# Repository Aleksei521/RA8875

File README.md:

# RA8875
 Board and font convertor for chip RA8875
 https://habr.com/ru/post/551820/#habracut

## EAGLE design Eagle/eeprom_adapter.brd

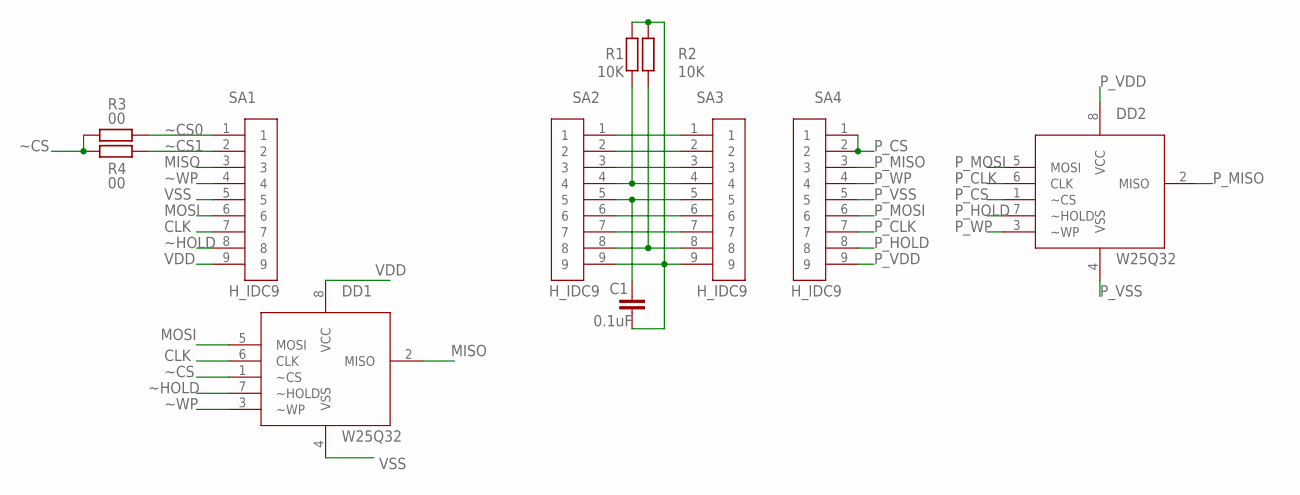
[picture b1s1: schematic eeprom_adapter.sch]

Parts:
C1: 0.1uF; C0603
DD1: W25Q32; SOIC-208
DD2: W25Q32; H_DIL08
R1, R2: 10K; R0603
R3, R4: 00; R0603
SA1, SA2, SA3, SA4: H_IDC9; H_IDC8X1_27

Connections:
CLK: DD1.6 (CLK), SA1.7
MISO: DD1.2 (MISO), SA1.3
MOSI: DD1.5 (MOSI), SA1.6
unnamed: SA2.1, SA3.1
unnamed: SA2.2, SA3.2
unnamed: SA2.3, SA3.3
unnamed: R1.1, SA2.4, SA3.4
unnamed: C1.1, SA2.5, SA3.5
unnamed: SA2.6, SA3.6
unnamed: SA2.7, SA3.7
unnamed: R2.1, SA2.8, SA3.8
unnamed: C1.2, R1.2, R2.2, SA2.9, SA3.9
P_CLK: DD2.6 (CLK), SA4.7
P_CS: DD2.1 (~CS), SA4.1, SA4.2
P_HOLD: DD2.7 (~HOLD), SA4.8
P_MISO: DD2.2 (MISO), SA4.3
P_MOSI: DD2.5 (MOSI), SA4.6
P_VDD: DD2.8 (VCC), SA4.9
P_VSS: DD2.4 (VSS), SA4.5
P_WP: DD2.3 (~WP), SA4.4
VDD: DD1.8 (VCC), SA1.9
VSS: DD1.4 (VSS), SA1.5
~CS: DD1.1 (~CS), R3.2, R4.2
~CS0: R3.1, SA1.1
~CS1: R4.1, SA1.2
~HOLD: DD1.7 (~HOLD), SA1.8
~WP: DD1.3 (~WP), SA1.4

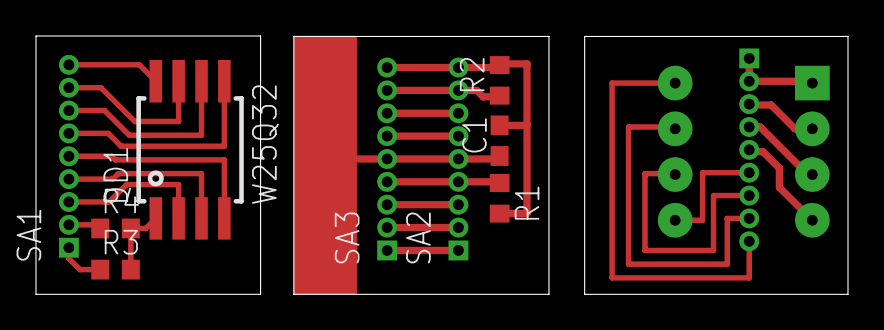
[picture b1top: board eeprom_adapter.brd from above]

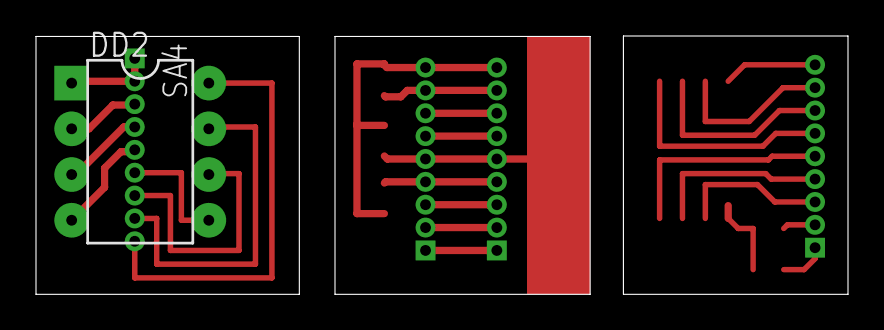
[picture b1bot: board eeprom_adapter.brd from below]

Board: 2 copper layers, 45.1 x 14.4 mm, 11 parts (2 on the bottom side), 27 nets.

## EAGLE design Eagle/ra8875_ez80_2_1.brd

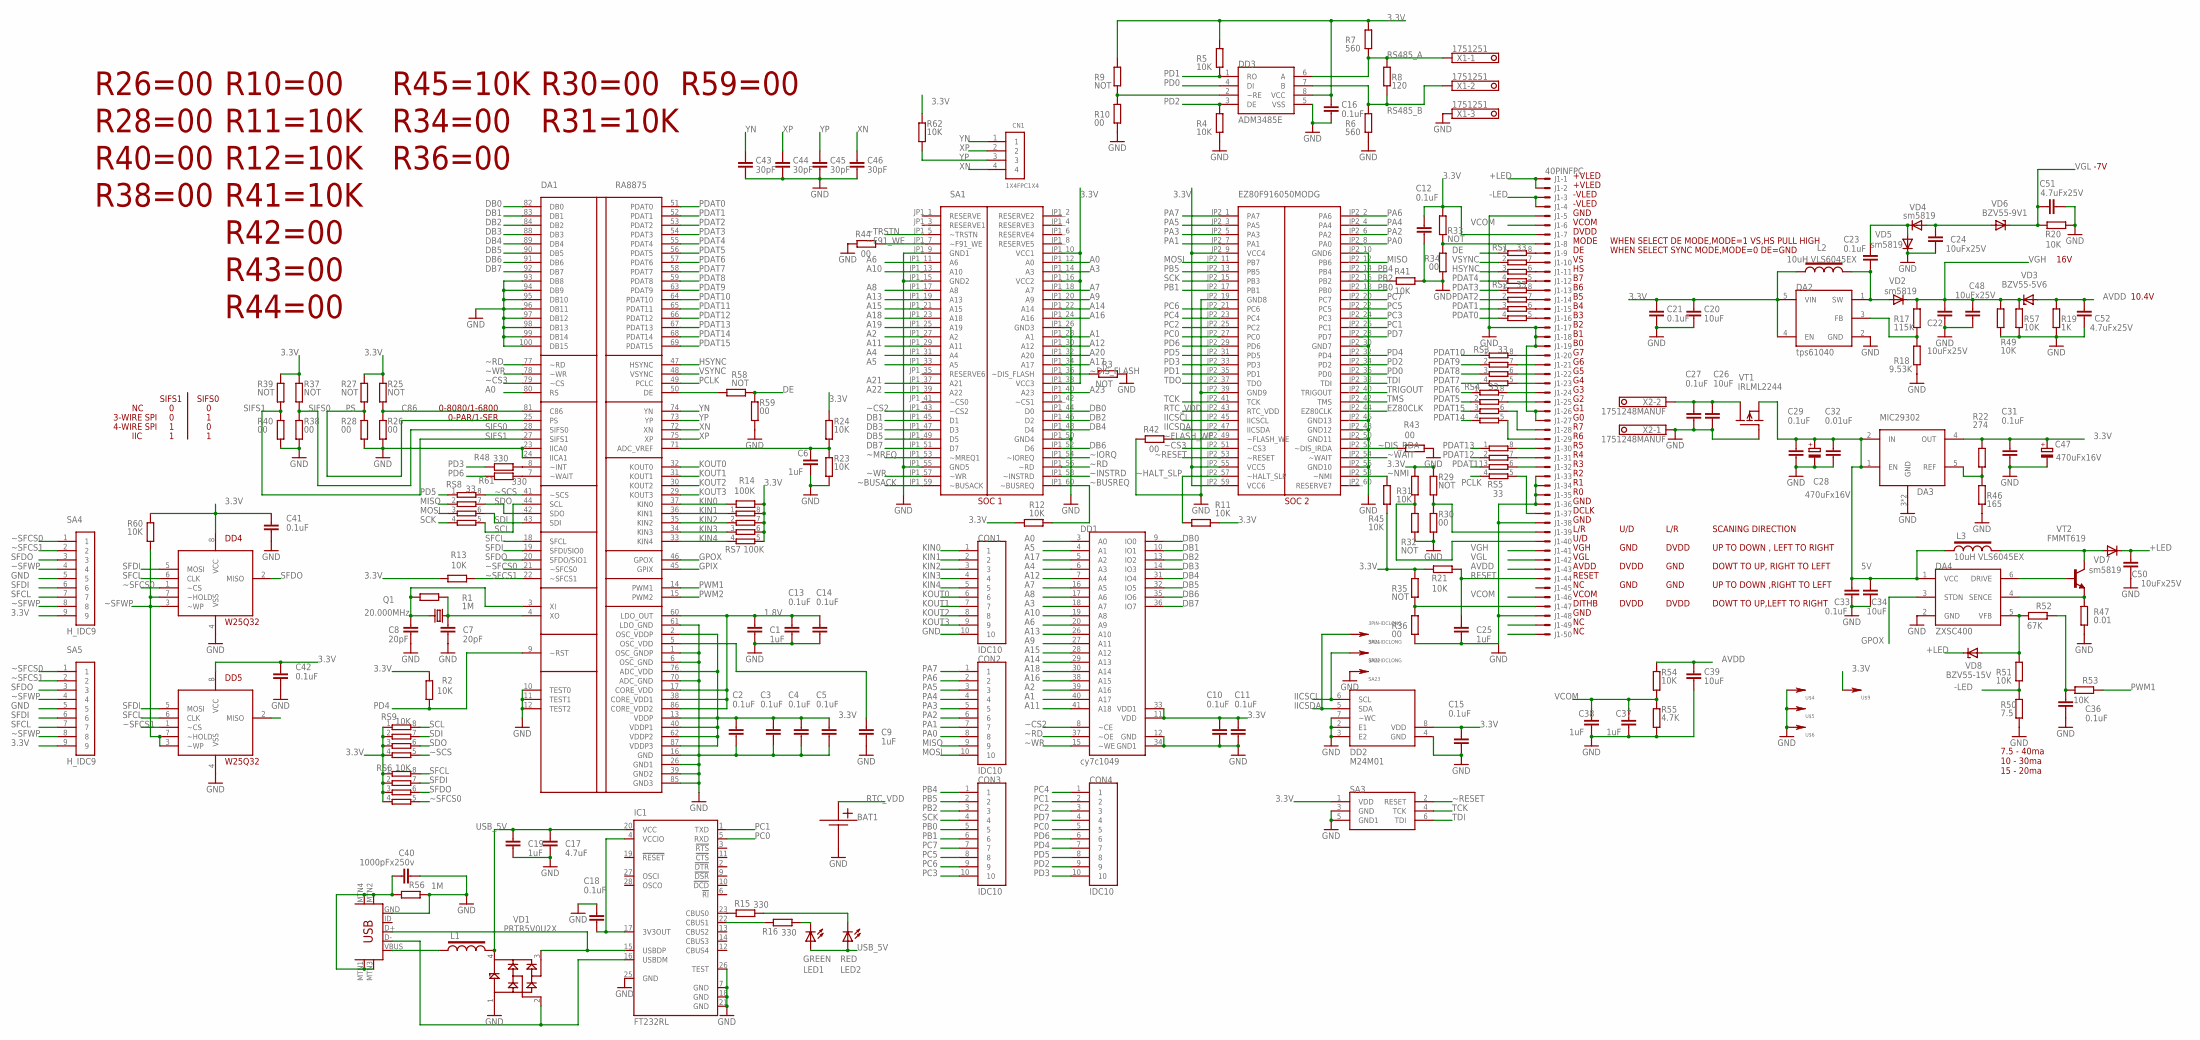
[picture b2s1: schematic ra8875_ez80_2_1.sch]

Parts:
BAT1: EECF5R5U155
C1, C6, C9, C19, C25, C37, C38: 1uF; C0603
C2, C3, C4, C5, C10, C11, C12, C13, C14, C15, C16, C18, C41, C42: 0.1uF; C0603
C7, C8: 20pF; C0805
C17: 4.7uF; C0805
C20, C26, C34, C39: 10uF; C1206
C21, C27, C29, C31, C33, C36: 0.1uF; C0805
C22, C24, C48, C50: 10uFx25V; C1206
C23: 0.1uF; C1206
C28, C47: 470uFx16V; SMC_D
C32: 0.01uF; C0805
C40: 1000pFx250v; C1812
C43, C44, C45, C46: 30pF; C0603
C51, C52: 4.7uFx25V; C1206
CN1: 1X4FPC1X4; FPC_1MM-4
CON1, CON2, CON3, CON4: IDC10
DA1: RA8875; LQFP100
DA2: tps61040; SOT23-5L
DA3: MIC29302; TO263-5
DA4: ZXSC400; SOT23-6L
DD1: cy7c1049; TSOP_Z44_II
DD2: M24M01; SOIC8
DD3: ADM3485E; SO8
DD4, DD5: W25Q32; SOIC-208
IC1: FT232RL; SSOP28
J1: 40PINFPC; 4-1734839-0
L1: USB_INDUCTOR; R0805
L2, L3: 10uH VLS6045EX; VLS6045
LED1: GREEN; CHIPLED_1206
LED2: RED; CHIPLED_1206
Q1: 20.000MHz; HC49U70
R1: 1M; R0603
R2, R4, R5, R11, R12, R13, R21, R23, R24, R31, R41, R45, R51, R53, R54, R60, R62: 10K; R0603
R3, R9, R25, R27, R29, R32, R33, R35, R37, R39, R58: NOT; R0603
R6, R7: 560; R0603
R8: 120; R0603
R10, R26, R28, R30, R34, R36, R38, R40, R42, R43, R44, R59: 00; R0603
R14: 100K; R0603
R15, R16, R48, R61: 330; R0603
R17: 115K; R0805
R18: 9.53K; R0805
R19: 1K; R0805
R20: 10K; R0805
R22: 274; R0805
R46: 165; R0805
R47: 0.01; R2512
R49, R57: 10K; R1206
R50: 7.5; R0805
R52: 67K; R0603
R55: 4.7K; R0603
R56: 1M; R1206
RS1, RS2, RS3, RS4, RS5, RS8: 33; CAY16-4
RS6, RS9: 10K; CAY16-4
RS7: 100K; CAY16-4
SA1: EZ80F916050MODG
SA2: 3PIN-IDCLONG; 3PIN-254
SA3: ZPAKII
SA4, SA5: H_IDC9; H_IDC8X1_27
U$3: USB-MINIB-5PIN; USB-MINIB
U$4, U$5, U$6, U$9: 1-PIN2_54; 1_PIN_2_54
VD1: PRTR5V0U2X; SOT143B
VD2, VD4, VD5, VD7: sm5819; MELF-MLL41
VD3: BZV55-5V6; STABILITRON
VD6: BZV55-9V1; STABILITRON
VD8: BZV55-15V; STABILITRON
VT1: IRLML2244; SOT23
VT2: FMMT619; SOT23-BEC
X1: 1751251
X2: 1751248MANUF; 1751248

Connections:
1.8V: C1.1, C13.1, C14.1, DA1.17 (CORE_VDD), DA1.38 (CORE_VDD1), DA1.60 (LDO_OUT), DA1.86 (CORE_VDD2)
3.3V: C2.1, C3.1, C4.1, C5.1, C10.1, C11.1, C12.1, C15.1, C16.1, C20.1, C21.1, C31.1, C41.1, C42.1, C47.+, DA1.2 (OSC_VDDP), DA1.13 (VDDP), DA1.40 (VDDP1), DA1.62 (VDDP2), DA1.76 (ADC_VDD), DA1.87 (VDDP3), DA2.4 (EN), DA2.5 (VIN), DA3.4 (OUT), DD1.11 (VDD), DD1.33 (VDD1), DD2.8 (VDD), DD3.8 (VCC), DD4.8 (VCC), DD5.8 (VCC), J1.7 (MS), L2.P$1 (L1), R2.2, R5.1, R7.1, R9.1, R11.1, R12.2, R13.1, R14.2, R21.1, R22.1, R24.1, R25.1, R27.1, R29.1, R31.1, R33.1, R35.1, R37.1, R39.1, R45.2, R60.1, R62.1, RS6.1, RS6.2, RS6.3, RS6.4, RS7.5, RS7.6, RS7.7, RS7.8, RS9.1, RS9.2, RS9.3, RS9.4, SA1.JP1_10 (VCC1), SA1.JP1_16 (VCC2), SA1.JP1_38 (VCC3), SA1.JP2_9 (VCC4), SA1.JP2_55 (VCC5), SA1.JP2_59 (VCC6), SA3.1 (VDD), SA4.9, SA5.9, U$9.P$1
5V: C28.+, C29.1, C32.1, C33.1, C34.1, DA3.1 (EN), DA3.2 (IN), DA4.1 (VCC), L3.P$1 (L1), VT1.2 (S)
+LED: C50.1, J1.1 (MSV), J1.2 (MS), VD7.C, VD8.C
-LED: J1.3 (MS), J1.4 (MS), R50.1, R51.2
A0: DA1.80 (RS), DD1.3 (A0), SA1.JP1_12 (A0)
A1: DD1.40 (A17), SA1.JP1_28 (A1)
A2: DD1.39 (A16), SA1.JP1_27 (A2)
A3: DD1.18 (A7), SA1.JP1_14 (A3)
A4: DD1.6 (A3), SA1.JP1_31 (A4)
A5: DD1.4 (A1), SA1.JP1_33 (A5)
A6: DD1.20 (A9), SA1.JP1_11 (A6)
A7: DD1.16 (A5), SA1.JP1_18 (A7)
A8: DD1.17 (A6), SA1.JP1_17 (A8)
A9: DD1.27 (A11), SA1.JP1_20 (A9)
A10: DD1.19 (A8), SA1.JP1_13 (A10)
A11: DD1.41 (A18), SA1.JP1_29 (A11)
A12: DD1.7 (A4), SA1.JP1_30 (A12)
A13: DD1.26 (A10), SA1.JP1_19 (A13)
A14: DD1.29 (A13), SA1.JP1_22 (A14)
A15: DD1.28 (A12), SA1.JP1_21 (A15)
A16: DD1.38 (A15), SA1.JP1_24 (A16)
A17: DD1.5 (A2), SA1.JP1_34 (A17)
A18: DD1.30 (A14), SA1.JP1_23 (A18)
A19: SA1.JP1_25 (A19)
A20: SA1.JP1_32 (A20)
A21: SA1.JP1_37 (A21)
A22: SA1.JP1_39 (A22)
A23: SA1.JP1_40 (A23)
ADC_VREF: C6.1, DA1.71 (ADC_VREF), R23.1, R24.2
AVDD: C39.1, C52.1, J1.43 (MS), R19.1, R54.1, VD3.A
C86: DA1.81 (C86), R25.2, R26.1
DB0: DA1.82 (DB0), DD1.9 (IO0), SA1.JP1_44 (D0)
DB1: DA1.83 (DB1), DD1.10 (IO1), SA1.JP1_45 (D1)
DB2: DA1.84 (DB2), DD1.13 (IO2), SA1.JP1_46 (D2)
DB3: DA1.88 (DB3), DD1.14 (IO3), SA1.JP1_47 (D3)
DB4: DA1.89 (DB4), DD1.31 (IO4), SA1.JP1_48 (D4)
DB5: DA1.90 (DB5), DD1.32 (IO5), SA1.JP1_49 (D5)
DB6: DA1.91 (DB6), DD1.35 (IO6), SA1.JP1_52 (D6)
DB7: DA1.92 (DB7), DD1.36 (IO7), SA1.JP1_51 (D7)
DE: R58.1, R59.1, RS1.1
EZ80CLK: SA1.JP2_44 (EZ80CLK)
GND: BAT1.- (MINUS), C1.2, C2.2, C3.2, C4.2, C5.2, C6.2, C7.2, C8.2, C9.2, C10.2, C11.2, C12.2, C13.2, C14.2, C15.2, C16.2, C17.2, C18.1, C19.2, C20.2, C21.2, C22.2, C24.2, C25.2, C26.2, C27.2, C28.-, C29.2, C31.2, C32.2, C33.2, C34.2, C36.2, C37.2, C38.2, C39.2, C40.2, C41.2, C42.2, C43.2, C44.2, C45.2, C46.2, C47.-, C48.2, C50.2, C51.2, C52.2, CON1.10, DA1.1 (OSC_GNDP), DA1.6 (OSC_GND), DA1.10 (TEST0), DA1.11 (TEST1), DA1.12 (TEST2), DA1.16 (GND), DA1.23 (IICA0), DA1.24 (IICA1), DA1.26 (GND1), DA1.39 (GND2), DA1.61 (LDO_GND), DA1.70 (ADC_GND), DA1.85 (GND3), DA1.93 (DB8), DA1.94 (DB9), DA1.95 (DB10), DA1.96 (DB11), DA1.97 (DB12), DA1.98 (DB13), DA1.99 (DB14), DA1.100 (DB15), DA2.2 (GND), DA3.3 (GND), DA3.6 (GND), DA4.2 (GND), DD1.12 (GND), DD1.34 (GND1), DD2.2 (E1), DD2.3 (E2), DD2.4 (GND), DD2.7 (~WC), DD3.5 (VSS), DD4.4 (VSS), DD5.4 (VSS), IC1.7 (GND), IC1.18 (GND), IC1.21 (GND), IC1.25 (GND), IC1.26 (TEST), J1.5 (MS), J1.17 (MS), J1.18 (MS), J1.19 (MS), J1.26 (MS), J1.27 (MS), J1.33 (MS), J1.34 (MS), J1.35 (MS), J1.36 (MS), J1.38 (MS), J1.48 (MS), R3.2, R4.2, R6.2, R10.2, R18.2, R19.2, R20.2, R23.2, R26.2, R28.2, R30.2, R32.2, R34.2, R36.2, R38.2, R40.2, R41.2, R42.1, R43.2, R44.1, R46.2, R47.2, R49.2, R50.2, R55.2, R56.2, R57.2, R59.2, SA1.JP1_9 (GND1), SA1.JP1_15 (GND2), SA1.JP1_26 (GND3), SA1.JP1_50 (GND4), SA1.JP1_55 (GND5), SA1.JP2_10 (GND6), SA1.JP2_19 (GND8), SA1.JP2_30 (GND7), SA1.JP2_39 (GND9), SA1.JP2_46 (GND13), SA1.JP2_48 (GND12), SA1.JP2_50 (GND11), SA1.JP2_56 (GND10), SA2.3, SA3.3 (GND), SA3.5 (GND1), SA4.5, SA5.5, U$3.GND, U$4.P$1, U$5.P$1, U$6.P$1, VD1.1 (GND), VD5.C, VT1.1 (G), X1.3, X2.1
GPIX: DA1.45 (GPIX)
GPOX: DA1.46 (GPOX), DA4.3 (STDN)
HSYNC: DA1.47 (HSYNC), RS1.3
IICSCL: DD2.6 (SCL), SA1.JP2_45 (IICSCL), SA2.2
IICSDA: DD2.5 (SDA), SA1.JP2_47 (IICSDA), SA2.1
KIN0: CON1.1, DA1.37 (KIN0), R14.1
KIN1: CON1.2, DA1.36 (KIN1), RS7.1
KIN2: CON1.3, DA1.35 (KIN2), RS7.2
KIN3: CON1.4, DA1.34 (KIN3), RS7.3
KIN4: CON1.5, DA1.33 (KIN4), RS7.4
KOUT0: CON1.6, DA1.32 (KOUT0)
KOUT1: CON1.7, DA1.31 (KOUT1)
KOUT2: CON1.8, DA1.30 (KOUT2)
KOUT3: CON1.9, DA1.29 (KOUT3)
MISO: CON2.9, RS8.2, SA1.JP2_12 (PB6)
MOSI: CON2.10, RS8.3, SA1.JP2_11 (PB7)
unnamed: DD3.2 (~RE), R9.2, R10.1
unnamed: L1.1 (L1), U$3.VBUS
unnamed: IC1.16 (USBDM), U$3.D-, VD1.2 (IO1)
unnamed: C18.2, IC1.4 (VCCIO), IC1.17 (3V3OUT)
unnamed: IC1.15 (USBDP), U$3.D+, VD1.3 (IO2)
unnamed: C23.2, DA2.1 (SW), L2.P$2 (L2), VD2.A
unnamed: DA2.3 (FB), R17.2, R18.1
unnamed: C24.1, VD4.A, VD6.A
unnamed: C26.1, C27.1, VT1.3 (D), X2.2
unnamed: DA1.8 (~INT), R48.2
unnamed: DA3.5 (REF), R22.2, R46.1
unnamed: C8.1, DA1.3 (XI), Q1.1, R1.1
unnamed: C7.1, DA1.4 (XO), Q1.2, R1.2
unnamed: IC1.23 (CBUS0), R15.1
unnamed: C9.1, DA1.5 (OSC_VDD)
unnamed: C36.1, R52.2, R53.1
unnamed: J1.24 (MS), RS4.8
unnamed: J1.20 (MS), RS3.8
unnamed: J1.21 (MS), RS3.7
unnamed: J1.22 (MS), RS3.6
unnamed: J1.23 (MS), RS3.5
unnamed: J1.28 (MS), RS4.6
unnamed: J1.29 (MS), RS4.5
unnamed: J1.25 (MS), RS4.7
unnamed: J1.30 (MS), RS5.8
unnamed: J1.31 (MS), RS5.7
unnamed: DA4.5 (VFB), R51.1, R52.1, VD8.A
unnamed: C40.1, R56.1, U$3.MTN1 (MTN2), U$3.MTN2 (MTN3), U$3.MTN3 (MTN1), U$3.MTN4
unnamed: DA1.50 (DE), R58.2
unnamed: J1.47 (MS), R35.2, R36.1
unnamed: DA4.6 (DRIVE), VT2.B
unnamed: IC1.22 (CBUS1), R16.1
unnamed: LED2.C, R15.2
unnamed: LED1.C, R16.2
unnamed: L3.P$2 (L2), VD7.A, VT2.C
unnamed: C23.1, VD4.C, VD5.A
unnamed: J1.8 (MS), R33.2, R34.1
unnamed: DA1.7 (~WAIT), R61.2
unnamed: DA4.4 (SENCE), R47.1, VT2.E
unnamed: J1.32 (MS), RS5.6
unnamed: J1.37 (MS), RS5.5
unnamed: J1.9 (MS), RS1.8
unnamed: J1.10 (MS), RS1.7
unnamed: J1.11 (MS), RS1.6
unnamed: J1.12 (MS), RS1.5
unnamed: J1.13 (MS), RS2.8
unnamed: J1.14 (MS), RS2.7
unnamed: J1.15 (MS), RS2.6
unnamed: J1.16 (MS), RS2.5
unnamed: J1.39 (MS), R29.2, R30.1
unnamed: J1.40 (MS), R31.2, R32.1
PA0: CON2.8, SA1.JP2_8 (PA0)
PA1: CON2.7, SA1.JP2_7 (PA1)
PA2: CON2.6, SA1.JP2_6 (PA2)
PA3: CON2.5, SA1.JP2_5 (PA3)
PA4: CON2.4, SA1.JP2_4 (PA4)
PA5: CON2.3, SA1.JP2_3 (PA5)
PA6: CON2.2, SA1.JP2_2 (PA6)
PA7: CON2.1, SA1.JP2_1 (PA7)
PB0: CON3.5, SA1.JP2_18 (PB0)
PB1: CON3.6, SA1.JP2_17 (PB1)
PB2: CON3.3, R41.1, SA1.JP2_16 (PB2)
PB4: CON3.1, SA1.JP2_14 (PB4)
PB5: CON3.2, SA1.JP2_13 (PB5)
PC0: CON4.5, IC1.5 (RXD), SA1.JP2_27 (PC0)
PC1: CON4.2, IC1.1 (TXD), SA1.JP2_26 (PC1)
PC2: CON4.3, SA1.JP2_25 (PC2)
PC3: CON3.10, SA1.JP2_24 (PC3)
PC4: CON4.1, SA1.JP2_23 (PC4)
PC5: CON3.8, SA1.JP2_22 (PC5)
PC6: CON3.9, SA1.JP2_21 (PC6)
PC7: CON3.7, SA1.JP2_20 (PC7)
PCLK: DA1.49 (PCLC), RS5.4
PD0: DD3.4 (DI), SA1.JP2_36 (PD0)
PD1: DD3.1 (RO), R5.2, SA1.JP2_35 (PD1)
PD2: CON4.9, DD3.3 (DE), R4.1, SA1.JP2_34 (PD2)
PD3: CON4.10, R48.1, SA1.JP2_33 (PD3)
PD4: CON4.7, DA1.9 (~RST), R2.1, SA1.JP2_32 (PD4)
PD5: CON4.8, RS8.1, SA1.JP2_31 (PD5)
PD6: CON4.6, R61.1, SA1.JP2_29 (PD6)
PD7: CON4.4, SA1.JP2_28 (PD7)
PDAT0: DA1.51 (PDAT0), RS2.4
PDAT1: DA1.52 (PDAT1), RS2.3
PDAT2: DA1.53 (PDAT2), RS2.2
PDAT3: DA1.54 (PDAT3), RS2.1
PDAT4: DA1.55 (PDAT4), RS1.4
PDAT5: DA1.56 (PDAT5), RS4.2
PDAT6: DA1.57 (PDAT6), RS4.1
PDAT7: DA1.58 (PDAT7), RS3.4
PDAT8: DA1.59 (PDAT8), RS3.3
PDAT9: DA1.63 (PDAT9), RS3.2
PDAT10: DA1.64 (PDAT10), RS3.1
PDAT11: DA1.65 (PDAT11), RS5.3
PDAT12: DA1.66 (PDAT12), RS5.2
PDAT13: DA1.67 (PDAT13), RS5.1
PDAT14: DA1.68 (PDAT14), RS4.4
PDAT15: DA1.69 (PDAT15), RS4.3
PS: DA1.25 (PS), R27.2, R28.1
PWM1: DA1.14 (PWM1), R53.2
PWM2: DA1.15 (PWM2)
RESET: C25.1, J1.44 (MS), R21.2
RS485_A: DD3.6 (A), R7.2, R8.1, X1.1
RS485_B: DD3.7 (B), R6.1, R8.2, X1.2
RTC_VDD: BAT1.+ (PLUS), SA1.JP2_43 (RTC_VDD)
SCK: CON3.4, RS8.4, SA1.JP2_15 (PB3)
SCL: DA1.44 (SCL), RS8.5, RS9.8
SDI: DA1.43 (SDI), RS8.6, RS9.7
SDO: DA1.42 (SDO), RS8.7, RS9.6
SFCL: DA1.18 (SFCL), DD4.6 (CLK), DD5.6 (CLK), RS6.8, SA4.7, SA5.7
SFDI: DA1.19 (SFDI/SIO0), DD4.5 (MOSI), DD5.5 (MOSI), RS6.7, SA4.6, SA5.6
SFDO: DA1.20 (SFDO/SIO1), DD4.2 (MISO), DD5.2 (MISO), RS6.6, SA4.3, SA5.3
SIFS0: DA1.28 (SIFS0), R37.2, R38.1
SIFS1: DA1.27 (SIFS1), R39.2, R40.1
TCK: SA1.JP2_41 (TCK), SA3.4 (TCK)
TDI: SA1.JP2_38 (TDI), SA3.6 (TDI)
TDO: SA1.JP2_37 (TDO)
TMS: SA1.JP2_42 (TMS)
TRIGOUT: SA1.JP2_40 (TRIGOUT)
USB_5V: C17.1, C19.1, IC1.20 (VCC), L1.2 (L2), LED1.A, LED2.A, VD1.4 (VCC)
VCOM: C37.1, C38.1, J1.6 (MS), J1.46 (MS), R54.2, R55.1
VGH: C22.1, C48.1, J1.41 (MS), R17.1, R49.1, R57.1, VD2.C, VD3.C
VGL: C51.1, J1.42 (MS), R20.1, VD6.C
VSYNC: DA1.48 (VSYNC), RS1.2
XN: C46.1, CN1.4, DA1.72 (XN)
XP: C44.1, CN1.2, DA1.75 (XP)
YN: C43.1, CN1.1, DA1.74 (YN)
YP: C45.1, CN1.3, DA1.73 (YP), R62.2
~BUSACK: SA1.JP1_59 (~BUSACK)
~BUSREQ: R12.1, SA1.JP1_60 (~BUSREQ)
~CS2: DD1.8 (~CE), SA1.JP1_43 (~CS2)
~CS3: DA1.79 (~CS), SA1.JP2_51 (~CS3)
~DIS_FLASH: R3.1, SA1.JP1_36 (~DIS_FLASH)
~DIS_RDA: R43.1, SA1.JP2_52 (~DIS_IRDA)
~F91_WE: R44.2, SA1.JP1_7 (~F91_WE)
~FLASH_WE: R42.2, SA1.JP2_49 (~FLASH_WE)
~HALT_SLP: R11.2, SA1.JP2_57 (~HALT_SLP)
~INSTRD: SA1.JP1_58 (~INSTRD)
~IORQ: SA1.JP1_54 (~IOREQ)
~MREQ: SA1.JP1_53 (~MREQ1)
~NMI: R45.1, SA1.JP2_58 (~NMI)
~RD: DA1.77 (~RD), DD1.37 (~OE), SA1.JP1_56 (~RD)
~RESET: SA1.JP2_53 (~RESET), SA3.2 (RESET)
~SCS: DA1.41 (~SCS), RS8.8, RS9.5
~SFCS0: DA1.21 (~SFCS0), DD4.1 (~CS), RS6.5, SA4.1, SA5.1
~SFCS1: DA1.22 (~SFCS1), DD5.1 (~CS), R13.2, SA4.2, SA5.2
~SFWP: DD4.3 (~WP), DD4.7 (~HOLD), DD5.3 (~WP), DD5.7 (~HOLD), R60.2, SA4.4, SA4.8, SA5.4, SA5.8
~TRSTN: SA1.JP1_5 (~TRSTN)
~WAIT: SA1.JP2_54 (~WAIT)
~WR: DA1.78 (~WR), DD1.15 (~WE), SA1.JP1_57 (~WR)

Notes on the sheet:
0-PAR/1-SER
0-8080/1-6800
+VLED
-VLED
GND
VCOM
DVDD
MODE
DCLK
L/R
U/D
VGH
VGL
AVDD
RESET
DITHB
SCANING DIRECTION
UP TO DOWN , LEFT TO RIGHT
DOWT TO UP, RIGHT TO LEFT
DOWT TO UP,LEFT TO RIGHT
UP TO DOWN ,RIGHT TO LEFT
WHEN SELECT DE MODE,MODE=1 VS,HS PULL HIGH
WHEN SELECT SYNC MODE,MODE=0 DE=GND
SIFS0
SIFS1
3-WIRE SPI
4-WIRE SPI
IIC
10.4V
16V
-7V
R10=00
R11=10K
R12=10K
R41=10K
R42=00
R43=00
R44=00
R45=10K
R34=00

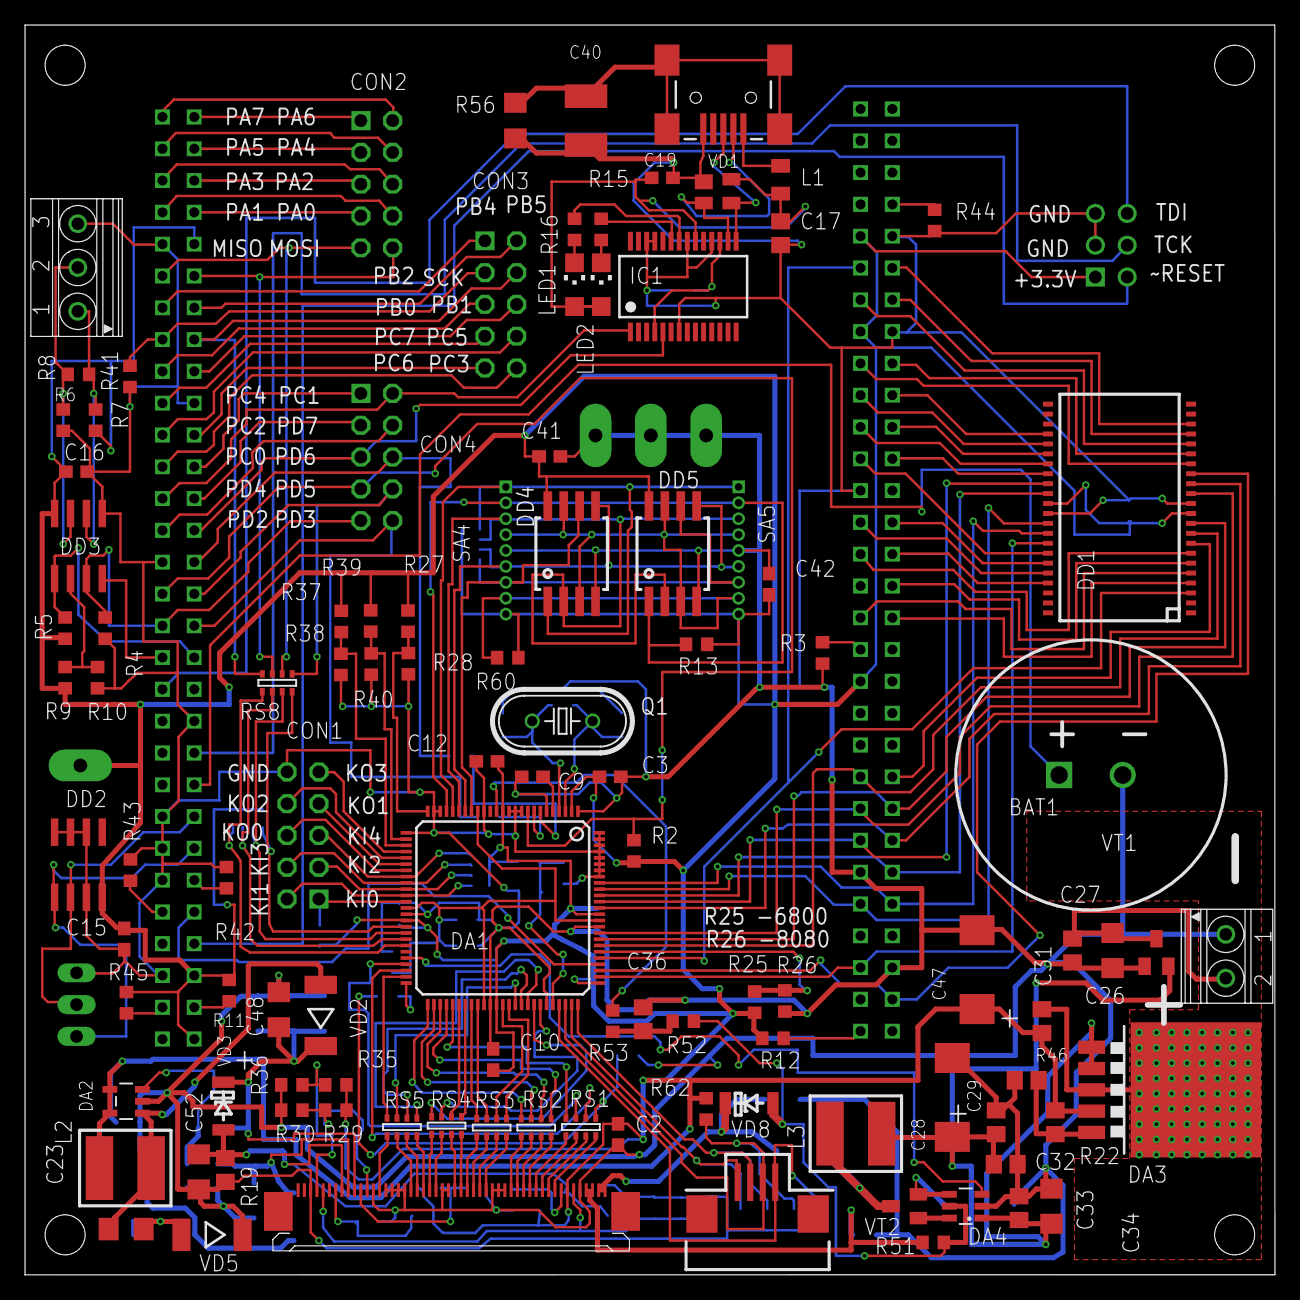
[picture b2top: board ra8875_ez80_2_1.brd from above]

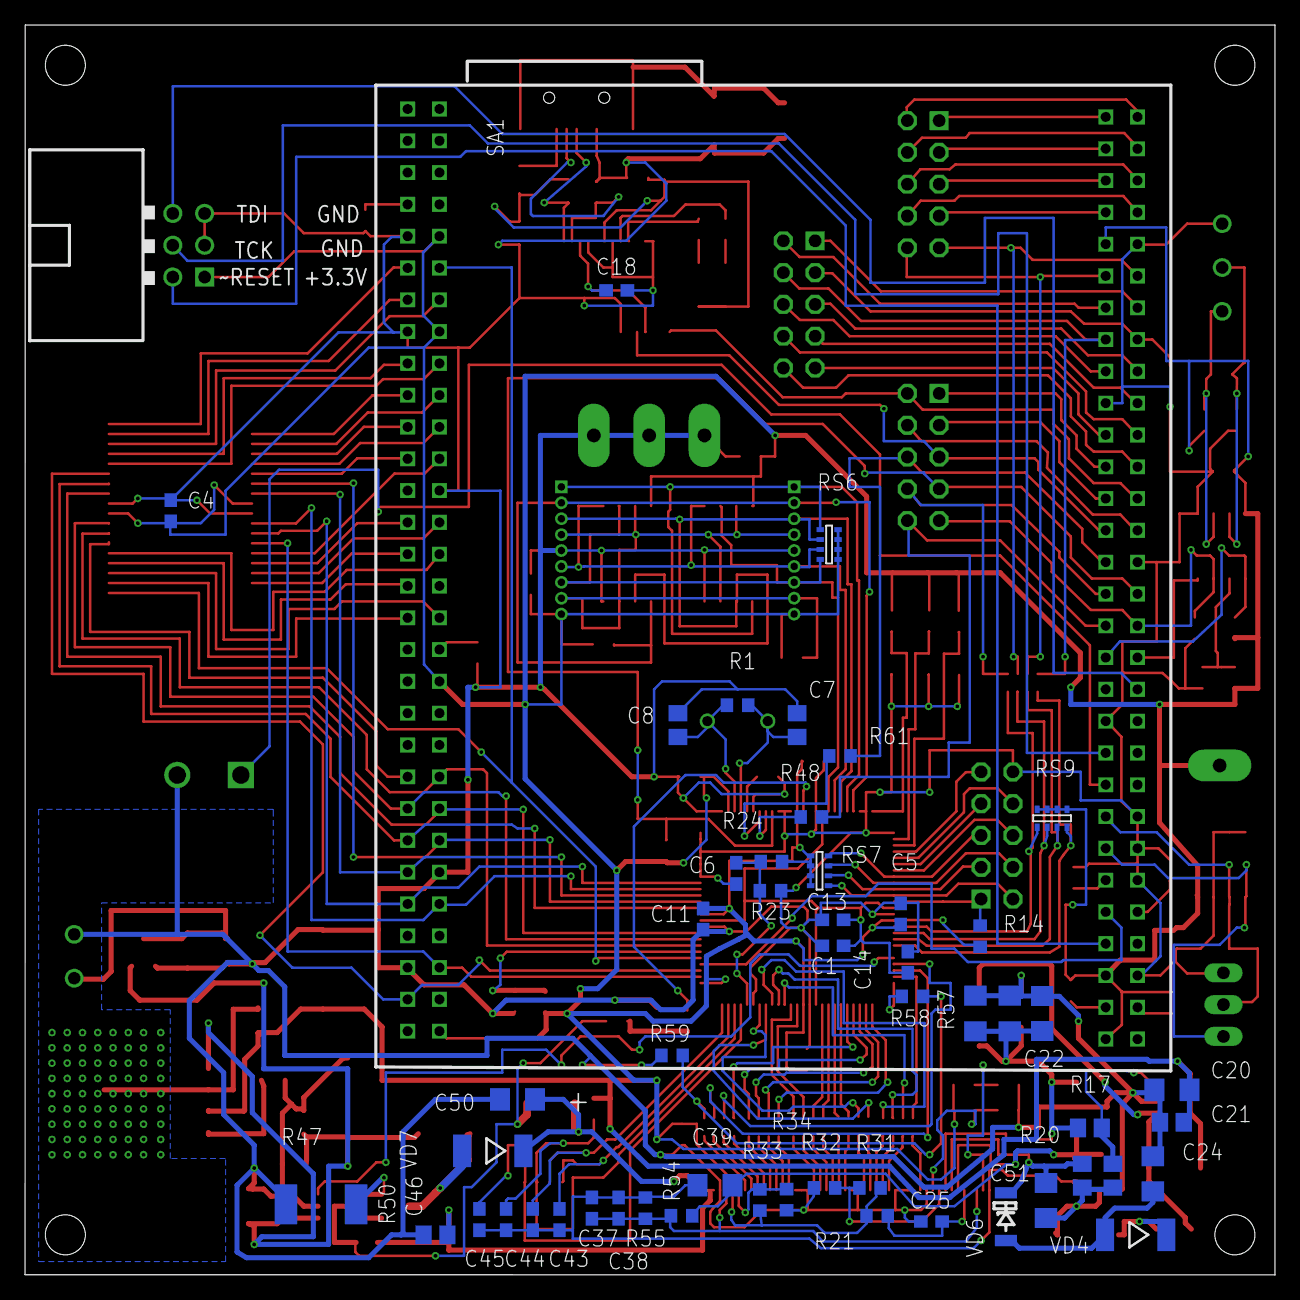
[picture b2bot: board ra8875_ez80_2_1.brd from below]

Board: 2 copper layers, 99.8 x 99.8 mm, 165 parts (54 on the bottom side), 191 nets.

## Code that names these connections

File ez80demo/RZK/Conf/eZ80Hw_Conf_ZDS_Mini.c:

/***********************************************************************************
 * File       :eZ80Hw_conf_ZDS_Mini.c
 *
 * Description: Defines the configurable system parameters
 *
 * Copyright 2017 ZiLOG Inc.  ALL RIGHTS RESERVED.
 *
 * This file contains unpublished confidential and proprietary information
 * of ZiLOG, Inc.
 * NO PART OF THIS WORK MAY BE DUPLICATED, STORED, PUBLISHED OR DISCLOSED 
 * IN ANY FORM WITHOUT THE PRIOR WRITTEN CONSENT OF ZiLOG, INC.
 * This is not a license and no use of any kind of this work is authorized
 * in the absence of a written license granted by ZiLOG, Inc. in ZiLOG's 
 * sole discretion 
 *********************************************************************************/

#include <eZ80.h>

#include "ZTypes.h"
#include "hw_defs.h"
#include "ZDS_Vars.h"

#ifdef _EZ80F91
void RZK_HW_Init( void )
{
	/*
	 * Ensure the Bus Mode registers are properly configured.
	 * This block of code can be removed once the ZDSII startup code
	 * initializes the Bus Mode control registers.
	 */
	CS0_BMC = CS0_BMC_INIT_PARAM;
	CS1_BMC = CS1_BMC_INIT_PARAM;
	CS2_BMC = CS2_BMC_INIT_PARAM;
	CS3_BMC = CS3_BMC_INIT_PARAM;

	/*
	* Reduce the Number of Wait states on Internal Flash
	 */
	FLASH_CTRL = (FLASH_CTRL & ~FLASH_CTRL_7_WS) | FLASH_CTRL_3_WS;

	/*
	 * GPIO Map for the eZ80F91_99C0942:
	 *
	 *		Port A	
	 *			PA0..PA7		All GPIOs are available to the user,
	 *							(Default setting = Mode 2, Input)
	 *		Port B
	 *			PB0..PB7		All GPIOs are available to the user,
	 *							(Default setting = Mode 2, Input)
	 *							Note: Push Button Switches 1..3 are connected to PB0..2
	 *		Port C
	 *			PC0			Modem (Uart 1) TxD, Mode 7, Alternate Function
	 *			PC1			Modem (Uart 1) RxD, Mode 7, Alternate Function
	 *			PC2			Modem (Uart 1) RTS, Mode 7, Alternate Function
	 *			PC3			Modem (Uart 1) CTS, Mode 7, Alternate Function
	 *			PC4			Modem (Uart 1) DTR, Mode 7, Alternate Function
	 *			PC5			Modem (Uart 1) DSR, Mode 7, Alternate Function
	 *			PC6			Modem (Uart 1) DCD, Mode 7, Alternate Function
	 *			PC7			Modem (Uart 1) RI,  Mode 7, Alternate Function
	 *		Port D
	 *			PD0			Console (Uart 0) TxD, Mode 7, Alternate Function
	 *			PD1			Console (Uart 0) RxD, Mode 7, Alternate Function
	 *			PD2			Console (Uart 0) RTS, Mode 7, Alternate Function
	 *			PD3			Console (Uart 0) CTS, Mode 7, Alternate Function
	 *			PD4			- available for user, Mode 2, Input
	 *			PD5			- available for user, Mode 2, Input
	 *			PD6			- available for user, Mode 2, Input
	 *			PD7			- available for user, Mode 2, Input
	 */
	PA_DR   = 0xFF;
	PA_DDR  = 0xFF;
	PA_ALT1 = 0x00;
	PA_ALT2 = 0x00;

	PB_DR   = 0xFF;
	PB_DDR  = 0xBF;		//	PB6    		RS232 Enable,  Mode 1, Output = 1
	PB_ALT1 = 0x00;
	PB_ALT2 = 0x00;

	PC_DR   = 0x00;
	PC_DDR  = 0xFF;
	PC_ALT1 = 0x00;
	PC_ALT2 = 0xFF;

	PD_DR   = 0xF0;
	PD_DDR  = 0xFF;
	PD_ALT1 = 0x00;
	PD_ALT2 = 0x0F;
}
#endif

#ifdef _EZ80F92
void RZK_HW_Init( void )
{
	/*
	 * Ensure the Bus Mode registers are properly configured.
	 * This block of code can be removed once the ZDSII startup code
	 * initializes the Bus Mode control registers.
	 */
	CS0_BMC = CS0_BMC_INIT_PARAM;
	CS1_BMC = CS1_BMC_INIT_PARAM;
	CS2_BMC = CS2_BMC_INIT_PARAM;
	CS3_BMC = CS3_BMC_INIT_PARAM;

	/*
	* Reduce the Number of Wait states on Internal Flash
	 */
	FLASH_CTRL = (FLASH_CTRL & ~FLASH_CTRL_7_WS) | FLASH_CTRL_1_WS;

	/*
	 * GPIO Map for the EZ80F920200ZCO
	 *
	 *		Port A	
	 *			PA0..PA7		Not Present
	 *		Port B
	 *			PB0..PB7		All GPIOs are available to the user,
	 *							(Default setting = Mode 2, Input)
	 *							Note: Push Button Switches 1..3 are connected to PB0..2
	 *		Port C
	 *			PC0			Modem (Uart 1) TxD, Mode 7, Alternate Function
	 *			PC1			Modem (Uart 1) RxD, Mode 7, Alternate Function
	 *			PC2			Modem (Uart 1) RTS, Mode 7, Alternate Function
	 *			PC3			Modem (Uart 1) CTS, Mode 7, Alternate Function
	 *			PC4			Modem (Uart 1) DTR, Mode 7, Alternate Function
	 *			PC5			Modem (Uart 1) DSR, Mode 7, Alternate Function
	 *			PC6			Modem (Uart 1) DCD, Mode 7, Alternate Function
	 *			PC7			Modem (Uart 1) RI,  Mode 7, Alternate Function
	 *		Port D
	 *			PD0			Console (Uart 0) TxD, Mode 7, Alternate Function
	 *			PD1			Console (Uart 0) RxD, Mode 7, Alternate Function
	 *			PD2			Console (Uart 0) RTS, Mode 7, Alternate Function
	 *			PD3			Console (Uart 0) CTS, Mode 7, Alternate Function
 	 *			PD4			CS8900A IRQ Line, 	 Mode 8, Interrupt actie high
	 *			PD5			- available for user, Mode 2, Input
	 *			PD6			CS8900A /LANLED Line, Mode 2, Input	   	(not used)
	 *			PD7			CS8900A /SLEEP Line,  Mode 1, Output = 1	(not used)
	 */
	PB_DR   = 0xFF;
	PB_DDR  = 0xFF;
	PB_ALT1 = 0x00;
	PB_ALT2 = 0x00;

	PC_DR   = 0x00;
	PC_DDR  = 0xFF;
	PC_ALT1 = 0x00;
	PC_ALT2 = 0xFF;

	PD_DR   = 0xF0;
	PD_DDR  = 0x6F;
	PD_ALT1 = 0x10;
	PD_ALT2 = 0x1F;
}

#endif


#ifdef _EZ80F93
void RZK_HW_Init( void )
{
	/*
    * Ensure the Bus Mode registers are properly configured
	 * There is a missing bracket in the definition of the CSx_BMC.
	 * Once this is corrected in a future ZDS release, it will be necessary to
	 * remove the extra bracker in the statements below.
	 */
	CS0_BMC = CS0_BMC_INIT_PARAM;
	CS1_BMC = CS1_BMC_INIT_PARAM;
	CS2_BMC = CS2_BMC_INIT_PARAM;
	CS3_BMC = CS3_BMC_INIT_PARAM;

	/*
    * Reduce the Number of Wait states on Internal Flash
	 */
	FLASH_CTRL = (FLASH_CTRL & ~FLASH_CTRL_7_WS) | FLASH_CTRL_1_WS;

	/*
	 * GPIO Map for the EZ80F93
	 *
	 *		Port A	
	 *			PA0..PA7		Not Present
	 *		Port B
	 *			PB0..PB7		All GPIOs are available to the user,
	 *							(Default setting = Mode 2, Input)
	 *							Note: Push Button Switches 1..3 are connected to PB0..2
	 *		Port C
	 *			PC0			Modem (Uart 1) TxD, Mode 7, Alternate Function
	 *			PC1			Modem (Uart 1) RxD, Mode 7, Alternate Function
	 *			PC2			Modem (Uart 1) RTS, Mode 7, Alternate Function
	 *			PC3			Modem (Uart 1) CTS, Mode 7, Alternate Function
	 *			PC4			Modem (Uart 1) DTR, Mode 7, Alternate Function
	 *			PC5			Modem (Uart 1) DSR, Mode 7, Alternate Function
	 *			PC6			Modem (Uart 1) DCD, Mode 7, Alternate Function
	 *			PC7			Modem (Uart 1) RI,  Mode 7, Alternate Function
	 *		Port D
	 *			PD0			Console (Uart 0) TxD, Mode 7, Alternate Function
	 *			PD1			Console (Uart 0) RxD, Mode 7, Alternate Function
	 *			PD2			Console (Uart 0) RTS, Mode 7, Alternate Function
	 *			PD3			Console (Uart 0) CTS, Mode 7, Alternate Function
	 *			PD4			CS8900A IRQ Line, 	 Mode 8, Interrupt actie high
	 *			PD5			- available for user, Mode 2, Input
	 *			PD6			CS8900A /LANLED Line, Mode 2, Input	   	(not used)
	 *			PD7			CS8900A /SLEEP Line,  Mode 1, Output = 1	(not used)
	 */
	PB_DR   = 0xFF;
	PB_DDR  = 0xFF;
	PB_ALT1 = 0x00;
	PB_ALT2 = 0x00;

	PC_DR   = 0x00;
	PC_DDR  = 0xFF;
	PC_ALT1 = 0x00;
	PC_ALT2 = 0xFF;

	PD_DR   = 0xF0;
	PD_DDR  = 0x6F;
	PD_ALT1 = 0x10;
	PD_ALT2 = 0x1F;

}

#endif


#ifdef _EZ80L92
void RZK_HW_Init( void )
{
	/*
	 * Ensure the Bus Mode registers are properly configured.
	 * This block of code can be removed once the ZDSII startup code
	 * initializes the Bus Mode control registers.
	 */
	CS_BMC0 = CS0_BMC_INIT_PARAM;
	CS_BMC1 = CS1_BMC_INIT_PARAM;
	CS_BMC2 = CS2_BMC_INIT_PARAM;
	CS_BMC3 = CS3_BMC_INIT_PARAM;

	/*
	 * GPIO Map for the EZ80L920210ZCO
	 *
	 *		Port A	
	 *			PA0..PA7		Not Present
	 *		Port B
	 *			PB0..PB7		All GPIOs are available to the user,
	 *							(Default setting = Mode 2, Input)
	 *							Note: Push Button Switches 1..3 are connected to PB0..2
	 *		Port C
	 *			PC0			Modem (Uart 1) TxD, Mode 7, Alternate Function
	 *			PC1			Modem (Uart 1) RxD, Mode 7, Alternate Function
	 *			PC2			Modem (Uart 1) RTS, Mode 7, Alternate Function
	 *			PC3			Modem (Uart 1) CTS, Mode 7, Alternate Function
	 *			PC4			Modem (Uart 1) DTR, Mode 7, Alternate Function
	 *			PC5			Modem (Uart 1) DSR, Mode 7, Alternate Function
	 *			PC6			Modem (Uart 1) DCD, Mode 7, Alternate Function
	 *			PC7			Modem (Uart 1) RI,  Mode 7, Alternate Function
	 *		Port D
	 *			PD0			Console (Uart 0) TxD, Mode 7, Alternate Function
	 *			PD1			Console (Uart 0) RxD, Mode 7, Alternate Function
	 *			PD2			Console (Uart 0) RTS, Mode 7, Alternate Function
	 *			PD3			Console (Uart 0) CTS, Mode 7, Alternate Function
	 *			PD4			CS8900A IRQ Line, 	 Mode 8, Interrupt actie high
	 *			PD5			- available for user, Mode 2, Input
	 *			PD6			CS8900A /LANLED Line, Mode 2, Input	   	(not used)
	 *			PD7			CS8900A /SLEEP Line,  Mode 1, Output = 1	(not used)
	 */
	PB_DR   = 0xFF;
	PB_DDR  = 0xFF;
	PB_ALT1 = 0x00;
	PB_ALT2 = 0x00;

	PC_DR   = 0x00;
	PC_DDR  = 0xFF;
	PC_ALT1 = 0x00;
	PC_ALT2 = 0xFF;

	PD_DR   = 0xF0;
	PD_DDR  = 0x6F;
	PD_ALT1 = 0x10;
	PD_ALT2 = 0x1F;
}

#endif

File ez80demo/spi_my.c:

#include "spi_my.h"
#include <stdio.h>
#include <ez80.h>
#include "ZTypes.h"
#include "ZSysgen.h"
#include "ZDevice.h"
#include "ZInterrupt.h"
#include "ZThread.h"
#include "ZSemaphore.h"

RZK_SEMAPHOREHANDLE_t SpiSemaphore;
RZK_THREADHANDLE_t ghSPI_isr;
#define SPI_ISR_STACK_SIZE		1024	/** stack size for the thread */
#define SPI_ISR_PRIORITY	6	    /** thread priority */

#define ENABLE_PIN_IRQ do{PB_ALT2|=0x40;}while(0)
#define DISABLE_PIN_IRQ do{PB_ALT2&=0xDF;}while(0)
#define SPI_SLAVE_PIN_SELECT do{PB_DR&=0xEF;}while(0) 
#define SPI_SLAVE_PIN_DESELECT do{PB_DR|=0x10;}while(0) 

#define IRQ_EN				 0x80
#define SPI_EN				 0x20
#define MASTER_EN			 0x10
#define CPOL				 0x08
#define CPHA				 0x04

#define SPIF				 0x80
#define WCOL				 0x40
#define MODF				 0x10

#define SPI_BUSY		     0x01

#define SPICMD_STATUS 1

#define SPICMD_STATUS_reset	8
#define SPICMD_STATUS_calibrate	4
#define SPICMD_STATUS_untouch	2
#define SPICMD_STATUS_touch	1
//STATUS output bytes
//STATUS bits
//0-touch detect
//1- untouch detect
//2- 1-calibrated 0-uncalibrated
//3- reset status 1-reset irq
//4-7 îñòàëîñü êîëè÷åñòâî òî÷åê â áóôåðå
//IRQ enable registr
//0-touch irq bit
//1- untouch irq bit
//X point LSByte
//X point MSbyte
//Y point LSByte
//Y point MSByte
#define SPICMD_CALIBRATE 2
//SPICMD_CALIBRATE input bytes
//number point (1..5),0-reset calibrate
//display X point LSByte
//display X point MSByte
//display Y point LSByte
//display Y point MSByte
//touch X point LSByte
//touch X point MSByte
//touch Y point LSByte
//touch Y point MSByte
#define SPICMD_IRQENABLE 3
//IRQ ENABLE 1-ENABLE IRQ
#define SPICMD_IRQDISABLE 4
//input bytes
//IRQ ENABLE 1-DISABLE IRQ
#define SPICMD_SLEEP 5
#define SPICMD_RESET 6
volatile UINT8 spi_tx_buf[16];
volatile UINT8 spi_rx_buf[16];
volatile UINT8 *spi_tx_ptr;
volatile UINT8 *spi_rx_ptr;
volatile UINT8 spi_tx_cnt;
volatile UINT8 spi_rx_cnt;
void (*p_touch_gui)(INT16 x,INT16 y,UINT8 state);

enum {SpiIdle,SpiStatus,SpiCalibrate,SpiIrqEnable,SpiIrqDisable,SpiSleep,SpiReset} volatile e_spi_state=SpiIdle;

extern void spi_pin_isr(void);
extern void spi_isr(void);
void SpiIsrTask(void);

void spi_open(void(*touch_gui)(INT16 x,INT16 y,UINT8 state))
{
//PB3 SCK
//PB2 ~SS input 10k to vdd
//PB6 MISO
//PB7 MOSI
//ALT2-1,ALT1-0,DDR-1,DR-0
//PB4 ~SS output
//ALT2-0,ALT1-1,DDR-0,DR-1
//PB5 IRQ input active High level
//ALT2-1,ALT1-1,DDR-0,DR-1

//ALT2 or 0xEC and 0xEF	
//ALT1 or 0x30 and 0x33
//DDR or 0xCC and 0xCF
//DR or 0x30 and 0x33
	RZKInstallInterruptHandler( (RZK_FNP_ISR)spi_pin_isr, PORTB5_IVECT ) ;
	RZKInstallInterruptHandler( (RZK_FNP_ISR)spi_isr, SPI_IVECT ) ;
	PB_DR&=0x33;
	PB_DR|=0x30;
	PB_DDR&=0xCF;
	PB_DDR|=0xCC;
	PB_ALT1&=0x33;
	PB_ALT1|=0x30;
	PB_ALT2&=0xEF;
	PB_ALT2|=0xEC;
	SPI_BRG_L=25;
	SPI_BRG_H=0;
	SPI_CTL=0x24;
	SPI_CTL|=IRQ_EN;
	p_touch_gui=touch_gui;
	ghSPI_isr = RZKCreateThreadEnhanced(( RZK_NAME_t *) "SPI_ISR",
					(RZK_PTR_t)SpiIsrTask,
					NULL,
					SPI_ISR_STACK_SIZE,
					SPI_ISR_PRIORITY,
					0, 
					RZK_THREAD_PREEMPTION | RZK_THREAD_INTERRUPT,0  ) ; 
	if( ghSPI_isr == NULL )
	{
		printf("\nUnable to create the SPI interrupt thread "); 
		RZKFormatError( RZKGetErrorNum() ) ;
		return ;
	}
	SpiSemaphore=RZKCreateSemaphore((RZK_NAME_t [])"SPI SEMAPHORE",1,RECV_ORDER_PRIORITY);
	if( SpiSemaphore == NULL )
	{
		printf("\nUnable to create the SPI semaphore "); 
		RZKFormatError( RZKGetErrorNum() ) ;
		return ;
	}
}

void SpiSendCmd(UINT8 cmd)
{
	RZKAcquireSemaphore(SpiSemaphore,MAX_INFINITE_SUSPEND);
	switch(cmd)
	{
		case SpiStatus:
			e_spi_state=SpiStatus;
			break;
		case SpiCalibrate:
			e_spi_state=SpiCalibrate;
			break;
		case SpiIrqEnable:
			e_spi_state=SpiIrqEnable;
			break;
		case SpiIrqDisable:
			e_spi_state=SpiIrqDisable;
			break;
		case SpiSleep:
			e_spi_state=SpiSleep;
			break;
		case SpiReset:
			e_spi_state=SpiReset;
			break;
		default: e_spi_state=SpiIdle;
		}
}
void SpiIsrTask(void)
{
	while(1)
	{
		switch(e_spi_state)
		{
			case SpiStatus:
				p_touch_gui(1,2,3);
				RZKReleaseSemaphore(SpiSemaphore);
				break;
			case SpiCalibrate:
				break;
			case SpiIrqEnable:
				break;
			case SpiIrqDisable:
				break;
			case SpiSleep:
				break;
			case SpiReset:
				break;
		}
		e_spi_state=SpiIdle;
		RZKSuspendInterruptThread();
	}
}
/*
void interrupt spi_isr(void)
{
	if(SPI_SR&SPIF)
	{
		if(spi_tx_cnt)
		{
			spi_tx_cnt--;
			if(spi_tx_cnt)
			{	
				spi_tx_ptr++;
				SPI_TSR=*spi_tx_ptr;
			}
			else
			{
				SPI_SLAVE_PIN_DESELECT;
				asm("NOP");
				asm("NOP");
				asm("NOP");
				asm("NOP");
				SPI_SLAVE_PIN_SELECT;
				SPI_TSR=0xAA;//read marker
			}
		}
		else
		{
			*spi_rx_ptr=SPI_RBR;
			spi_rx_ptr++;
			spi_rx_cnt--;
			if(spi_rx_cnt)
			{
				SPI_TSR=0xAA;//read marker
			}
			else
			{
				SPI_SLAVE_PIN_DESELECT;
				//Îáðàáîòêà
			}
		}
	}
}*/

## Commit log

2021-04-11 Release
    Release
2021-04-11 add images
2021-04-11 add ez80 module datasheet
2021-04-11 add ez80 demo
2021-04-11 add gerber files
2021-04-12 change ez80 demo for compare speed soft and hardware fonts
2021-04-12 add url descrition
